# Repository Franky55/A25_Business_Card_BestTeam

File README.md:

# C3I A25\_Business\_Card

Concours de Conception de Circuits Imprimés – Université de Sherbrooke, Automne 2025

## Thème : Carte professionnelle (Business Card)

Bienvenue à la compétition de conception de PCB de l’Université de Sherbrooke, édition automne 2025 !
Cette année, le défi est de transformer la carte professionnelle traditionnelle en un **objet électronique unique, créatif et fonctionnel**.
Votre mission : concevoir un PCB au format carte de visite qui intègre des fonctionnalités innovantes, esthétiques et utiles dans un contexte professionnel réel.

---

## Déroulement

* **25 août** : Lancement de la compétition et ouverture des inscriptions
* **3 octobre** : Date limite d’inscription
* **10 octobre** : Date limite de sélection d’idée (formulaire fourni sur GitHub et Discord)
* **25 août au 31 décembre 23h59** : Période de conception et développement
* **Dates de commande des PCB et pièces** :

  * 19 septembre\* (LCSC)
  * 3 octobre\* (LCSC)
  * 17 octobre\* (LCSC)
  * 31 octobre\* (LCSC)
  * 14 novembre
  * 28 novembre
  * 12 décembre\*\* (commande finale, réception non garantie avant la fin)
* **Décembre** : Finalisation des projets
* **31 décembre 23h59** : Remise finale (schémas, Gerber, BOM, photos, doc)
* **5 janvier 2026** : Journée de l’événement et présentations publiques

---

### Répertoire "Template"  
Le répertoire "Template" contient tous les documents à remplir pour participer à la compétition. Vous y trouverez :  
- Formulaire d'idée (à remplir)
- Formulaire d'inscription (à remplir)
- Condition et termes de l'inscription
- TEMPLATE de PowerPoint
- TEMPLATE pour la documentation

---

### Répertoires code, elec et mech  
Chacun de ces répertoires contient de la documentation de départ pour vous guider. Consultez la section "doc". Ces répertoires sont également là pour vous aider à vous organiser lors du développement de votre règle.

---

### Comment forker le dépôt

1. Accédez au dépôt GitHub officiel à l'adresse suivante : `https://github.com/CCI-udes/H25_Pomodoro`.
2. Cliquez sur le bouton "Fork" en haut à droite de la page du dépôt.
3. Sélectionnez votre propre compte GitHub comme destination du fork.
4. Clonez le dépôt forké sur votre machine locale en utilisant la commande suivante :
   ```bash
   git clone https://github.com/<votre-utilisateur>/E25_Wearable.git
   ```

---

## Règlement

* Équipes de **1 à 3 personnes**
* Frais de participation : **10 \$ / membre** OU **courriel de commandite** (gabarits fournis)
* Dimensions maximales PCB : **88,9 mm x 50,8 mm**
* BOM maximum : **50 \$**
* Coût de développement total : **125 \$**
* Utilisation de **DevBoard permise** (pénalité de points si dans la version finale)
* Tous les types de composants acceptés (Bluetooth, NFC, OLED, etc.)
* Batterie rechargeable permise si formation suivie et protocole respecté
* Objectif : **s’amuser et apprendre** !

---

## Remise

Chaque équipe doit fournir via son fork GitHub :

* Schéma électrique (PDF)
* Fichiers Gerber du PCB + projet EDA OU PDF coloré des couches
* Photo(s) du PCB assemblé (avec et sans boîtier)
* BOM conforme aux normes C3I
* Documentation complète du projet

---

## Évaluation

Les projets seront notés sur un total de **250 points**, selon :

* **Idée \[15 pts]** (juges + vote des participants)
* **Fonctionnalité \[35 pts]** (implémentation et compréhension)
* **Complexité \[45 pts]** (hardware + software)
* **Gestion des ressources \[25 pts]** (BOM + commandes)
* **Démonstration \[55 pts]** (oral, écrit, esthétique)
* **Conception électronique \[75 pts]** (choix composants, schéma, PCB, assemblage, soudures)

---

## Prix

* 🏆 **Prix de conception** – Total 250 pts
* ⚡ **Prix du gningnégnieur** – Total 170 pts (créativité et apprentissage valorisés)
* 💼 **Prix du vendeur** – Total 125 pts (gestion, organisation, finition)

---

## Ressources utiles

* **Microcontrôleurs recommandés** : ESP32-C3, ESP32-S3, RP2040, RP2350, ch32v003
* **Logiciels de conception** : KiCad, Altium, EasyEDA (+ tutoriels fournis dans le doc)
* **Idées de business cards électroniques** : [Hackaday](https://hackaday.com/tag/pcb-business-card/), [Reddit](https://www.reddit.com/r/PCB/comments/14jk8cz/pcb_business_card_ideas/), [Exemples NFC](https://www.instructables.com/PCB-Business-Card-With-NFC/)
* **Discord** : [Lien d’invitation](https://discord.gg/xeSqf3N3Hw)

---

## Contacts

* Jacob Turcotte – Président – `Jacob.Turcotte@usherbrooke.ca`
* Miriam Caisse – Vice-présidente – `Miriam.Caisse@usherbrooke.ca`
* Jordan Gagnon – Trésorier – `Jordan.Gagnon@usherbrooke.ca`
* Céleste-Lyi Martel – Marketing – `Celeste-lyi.martel@usherbrooke.ca`

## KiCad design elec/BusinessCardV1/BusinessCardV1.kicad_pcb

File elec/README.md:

# Répertoire "elec" - CCI UdeS A24_ruler

Bienvenue dans le répertoire `elec` du projet **A24_ruler** pour la compétition de conception de PCB de l'Université de Sherbrooke, automne 2024.

## Objectif

Ce répertoire est destiné à contenir toute la documentation et les fichiers nécessaires à la conception électronique de la "règle" que vous allez créer pour cette compétition. Vous y trouverez des schémas, des fichiers de conception de PCB, et des ressources pour vous aider à concevoir et à réaliser vos circuits imprimés.

## Ressources

- [KiCad](https://www.kicad.org/) : Outil open-source pour la conception de PCB.
- [EasyEDA](https://easyeda.com/) : Outil de conception de PCB en ligne avec une interface conviviale.
- [Altium Designer](https://www.altium.com/altium-designer) : Solution professionnelle pour la conception de PCB avec des fonctionnalités avancées.

- [Digi-Key](https://www.digikey.com/) : Distributeur de composants électroniques.
- [Mouser Electronics](https://www.mouser.com/) : Distributeur de composants électroniques.
- [LCSC](https://www.lcsc.com/) : Distributeur de composants électroniques avec des prix compétitifs.

## Contributions

Lorsque vous apportez des modifications, assurez-vous de :
- Créer une branche spécifique pour vos changements.
- Soumettre une pull request une fois que vous êtes prêt pour une revue de code.

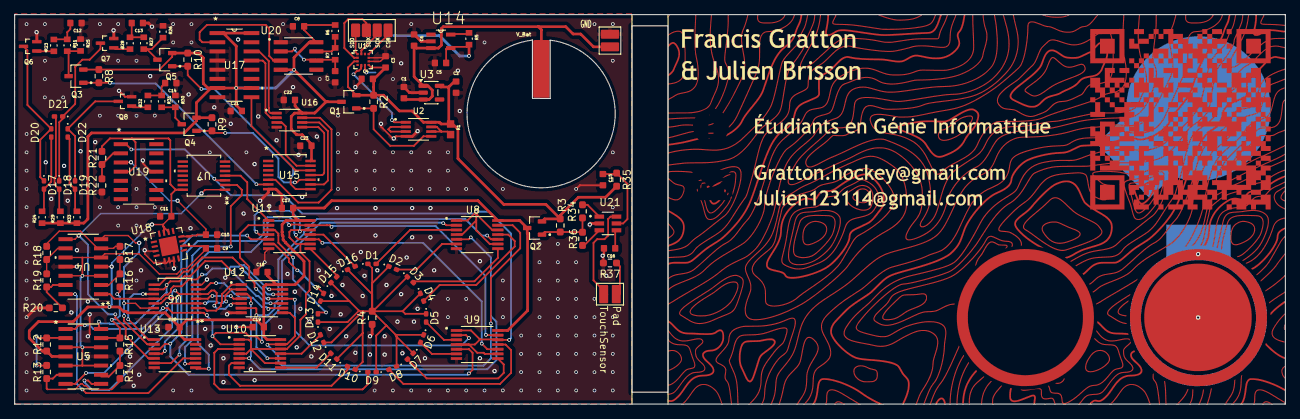
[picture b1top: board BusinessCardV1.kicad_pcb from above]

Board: 2 copper layers, 176.2 x 54.0 mm, 117 parts (1 on the bottom side), 102 nets.

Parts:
C1, C2, C3, C4, C8, C12, C13, C14, C17, C18, C19, C20, C21, C22, C23: 1uf; CAPC1608X90N
C5, C6: 4u7; CAPC1608X90N
C7: 1u; CAPC1608X90N
C9, C10, C11: CL10C471JB8NNNC; CAPC1608X90N
C15: 4.7uf; CAPC1608X90N
C16: 10uf; CAPC1608X90N
D1, D2, D3, D4, D5, D6, D7, D8, D9, D10, D11, D12, D13, D14, D15, D16, D17, D18, D19, D20, D21, D22: QBLP595-R; LED_0402_1005Metric_Pad0.77x0.64mm_HandSolder
J1: 61300411121; HEADER1x4_SMD
J2, J3, J4: 6130XX11121_61300211121; Header1x2_SMD
J5: 6130XX11121_61300211121; SMD_Header
Q1, Q2, Q3, Q4, Q5: DMG2305UX-7; SOT91P240X110-3N_DMG2305UX-7
Q6, Q7, Q8: DMG1012UW-7; SOT65P222X110-3N
R1: 100k; RESC1607X60N
R2, R3, R8, R9, R10: 1M; R_0603_1608Metric_Pad0.98x0.95mm_HandSolder
R4: 680; R_0603_1608Metric_Pad0.98x0.95mm_HandSolder
R5: 69K8; RESC1608X55N
R6: 20k; RESC1608X55N
R7: 700k; RESC1608X55N
R11, R27, R31: 250k; RESC1608X55N
R12, R13, R14, R15, R16, R17, R18, R19, R20, R21, R22, R34, R36, R37: 0; R_0603_1608Metric_Pad0.98x0.95mm_HandSolder
R23, R28, R32: 10; RESC1608X55N
R24, R29, R33: 180; RESC1608X55N
R25, R26, R30: 1.8M; RESC1608X55N
R35: 42.2; R_0603_1608Metric_Pad0.98x0.95mm_HandSolder
U1: *; XDCR_BMA400
U2: SN74LVC2G74DCTR; SOP65P400X130-8N
U3: TPS7A0233DBVR; SOT-23-5
U4, U5, U19: TLV8544DR; D14_TEX
U6, U7, U15: TC4069UBFTEL_N; TSSOP14_TOS
U8, U9, U10, U11, U12, U13: SN74LVC08APWR; SOP65P640X120-14N
U14: MCP73831T-2DCI_OT; SOT95P270X145-5N
U16: SN74LVC1G139DCTR; SOP65P400X130-8N
U17: SN74LV161ADR
U18: ADXL327BCPZ; CP_16_5A_ADI
U20: TLC555CDR; SOIC127P599X175-8N
U21: IQS228B00000000TSR; SOT95P280X100-6N
U22: TPD12S520DBT; design

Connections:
+3.3V: C2.2, C3.2, C4.2, Q1.2, Q2.2, R1.1, R2.1, R3.1, R35.2, U1.3 (VDDIO), U1.7 (VDD), U2.8 (VCC), U3.5 (OUT)
ADXL_X_OUT: C10.1, U18.12 (XOUT), U19.3 (+INA)
ADXL_Y_OUT: C9.1, U4.3 (+INA), U4.5 (+INB), U4.10 (+INC), U4.12 (+IND), U5.3 (+INA), U5.5 (+INB), U5.10 (+INC), U5.12 (+IND), U18.10 (YOUT)
Blue_LED: U15.5, U16.7 (Y0)
CLK_Sequence: U17.2 (CLK), U20.3 (OUT)
Charge_Blue_Cap: Q3.3, R11.2, R25.2
Charge_Green_Cap: Q5.3, R26.2, R27.2
Charge_Red_Cap: Q4.3, R30.2, R31.2
DISCH: R6.1, R7.2, U20.7 (DISCH)
GND: C1.1, C2.1, C3.1, C4.1, C5.1, C6.1, C7.1, C8.1, C9.2, C10.2, C11.1, C12.1, C13.1, C14.1, C15.2, C16.2, C17.1, C18.1, C19.1, C20.1, C21.1, C22.1, C23.1, J2.1, J3.1, Q6.2, Q7.2, Q8.2, R4.1, R20.2, R22.2, R25.1, R26.1, R30.1, R37.1, U1.8 (GNDIO), U1.9 (GND), U2.4 (GND), U3.2 (GND), U4.11 (V), U5.11 (V), U6.7, U7.7, U8.7 (GND), U9.7 (GND), U10.7 (GND), U11.7 (GND), U12.7 (GND), U13.7 (GND), U14.2 (VSS), U15.7, U16.4 (GND), U17.3 (A), U17.4 (B), U17.5 (C), U17.6 (D), U17.8 (GND), U18.3 (COM), U18.5 (COM), U18.6 (COM), U18.7 (COM), U19.11 (V), U20.1 (GND), U21.2 (GND)
Green_LED: U15.9, U16.6 (Y1)
INT_CLK: U1.5 (INT1), U2.1 (CLK)
LSB_Counter: U16.1 (A), U17.14 (QA)
MSB_Counter: U16.2 (B), U17.13 (QB)
unnamed: C12.2, R11.1, R23.2
unnamed: C13.2, R27.1, R28.2
unnamed: C14.2, R31.1, R32.2
unnamed: D1.2 (ANODE_(+)), U8.3 (1Y)
unnamed: D1.1 (CATHODE_(-)), D2.1 (CATHODE_(-)), D3.1 (CATHODE_(-)), D4.1 (CATHODE_(-)), D5.1 (CATHODE_(-)), D6.1 (CATHODE_(-)), D7.1 (CATHODE_(-)), D8.1 (CATHODE_(-)), D9.1 (CATHODE_(-)), D10.1 (CATHODE_(-)), D11.1 (CATHODE_(-)), D12.1 (CATHODE_(-)), D13.1 (CATHODE_(-)), D14.1 (CATHODE_(-)), D15.1 (CATHODE_(-)), D16.1 (CATHODE_(-)), R4.2
unnamed: D2.2 (ANODE_(+)), U8.6 (2Y)
unnamed: D3.2 (ANODE_(+)), U8.8 (3Y)
unnamed: D4.2 (ANODE_(+)), U8.11 (4Y)
unnamed: D5.2 (ANODE_(+)), U9.3 (1Y)
unnamed: D6.2 (ANODE_(+)), U9.6 (2Y)
unnamed: D7.2 (ANODE_(+)), U9.8 (3Y)
unnamed: D8.2 (ANODE_(+)), U9.11 (4Y)
unnamed: D9.2 (ANODE_(+)), U10.3 (1Y)
unnamed: D10.2 (ANODE_(+)), U10.6 (2Y)
unnamed: D11.2 (ANODE_(+)), U10.8 (3Y)
unnamed: D12.2 (ANODE_(+)), U10.11 (4Y)
unnamed: D13.2 (ANODE_(+)), U11.3 (1Y)
unnamed: D14.2 (ANODE_(+)), U11.6 (2Y)
unnamed: D15.2 (ANODE_(+)), U11.8 (3Y)
unnamed: D16.2 (ANODE_(+)), U11.11 (4Y)
unnamed: D17.2 (ANODE_(+)), D20.2 (ANODE_(+)), R24.2
unnamed: D17.1 (CATHODE_(-)), D20.1 (CATHODE_(-)), Q6.3
unnamed: D18.2 (ANODE_(+)), D21.2 (ANODE_(+)), R29.2
unnamed: D18.1 (CATHODE_(-)), D21.1 (CATHODE_(-)), Q7.3
unnamed: D19.2 (ANODE_(+)), D22.2 (ANODE_(+)), R33.2
unnamed: D19.1 (CATHODE_(-)), D22.1 (CATHODE_(-)), Q8.3
unnamed: Q6.1, R23.1
unnamed: Q7.1, R28.1
unnamed: Q8.1, R32.1
unnamed: R1.2, U2.6 (~CLR), U2.7 (~PRE)
unnamed: R16.2, R17.1, U4.2 (INA)
unnamed: R17.2, R18.1, U4.6 (INB)
unnamed: R18.2, R19.1, U4.9 (INC)
unnamed: R19.2, R20.1, U4.13 (IND)
unnamed: R12.2, R13.1, U5.2 (INA)
unnamed: R13.2, R14.1, U5.6 (INB)
unnamed: R14.2, R15.1, U5.9 (INC)
unnamed: R15.2, R16.1, U5.13 (IND)
unnamed: R5.1, U14.5 (PROG)
unnamed: R21.2, R22.1, U19.2 (INA)
unnamed: R36.2, U21.3 (CTRL/ND)
unnamed: R34.2, U21.1 (OUT)
unnamed: C15.1, R35.1, U21.5 (VDDHI)
unnamed: C16.1, U21.4 (VREG)
Pad: J4.2, R37.2
Power3V3: C8.2, C21.2, C22.2, C23.2, Q1.3, Q3.2, Q4.2, Q5.2, R6.2, R8.1, R9.1, R10.1, R24.1, R29.1, R33.1, U15.14, U16.8 (VCC), U17.1 (*CLR), U17.7 (ENP), U17.10 (ENT), U17.16 (VCC), U20.4 (RESET), U20.8 (VDD)
Q: Q1.1, R2.2, U2.5 (Q)
Red_LED: U15.11, U16.5 (Y2)
Reset: U15.13, U16.3 (Y3)
RingBTN: Q2.1, R3.2, R34.1, R36.1
RingPower: C11.2, C17.2, C18.2, C19.2, C20.2, Q2.3, R12.1, R21.1, U4.4 (V+), U5.4 (V+), U6.14, U7.14, U8.14 (VCC), U9.14 (VCC), U10.14 (VCC), U11.14 (VCC), U12.14 (VCC), U13.14 (VCC), U18.14 (VS), U18.15 (VS), U19.4 (V+)
SCX: J1.03, U1.12 (SCX)
SDO: J1.01, U1.1 (SDO)
SDX: J1.02, U1.2 (SDX)
SolarPower: C5.2, J2.2, R5.2, U14.4 (VDD)
TRIG: C7.2, R7.1, U20.2 (TRIG), U20.6 (THRES)
TouchSensor: J4.1, U21.6 (CX)
V_Bat: C1.2, C6.2, J3.2, J5.1, U3.1 (IN), U3.3 (EN), U14.3 (VBAT)
Y1: U5.1 (OUTA), U6.1, U8.2 (1B), U10.2 (1B)
Y2: U8.5 (2B), U10.5 (2B), U12.3 (1Y)
Y3: U8.10 (3B), U10.10 (3B), U12.6 (2Y)
Y4: U8.13 (4B), U10.13 (4B), U12.8 (3Y)
Y5: U9.2 (1B), U11.2 (1B), U12.11 (4Y)
Y6: U9.5 (2B), U11.5 (2B), U13.3 (1Y)
Y7: U9.10 (3B), U11.10 (3B), U13.6 (2Y)
Y8: U9.13 (4B), U11.13 (4B), U13.8 (3Y)
op_y2: U5.7 (OUTB), U6.3, U12.2 (1B)
op_y3: U5.8 (OUTC), U6.5, U12.5 (2B)
op_y4: U5.14 (OUTD), U6.9, U12.10 (3B)
op_y5: U4.1 (OUTA), U6.11, U12.13 (4B)
op_y6: U4.7 (OUTB), U6.13, U13.2 (1B)
op_y7: U4.8 (OUTC), U7.1, U13.5 (2B)
op_y8: U4.14 (OUTD), U13.10 (3B)
x: U7.3, U8.1 (1A), U8.4 (2A), U8.9 (3A), U8.12 (4A), U9.1 (1A), U9.4 (2A), U9.9 (3A), U9.12 (4A), U19.1 (OUTA)
~Blue_LED: Q3.1, R8.2, U15.6
~CSB: J1.04, U1.10 (~CSB)
~Green_LED: Q5.1, R10.2, U15.8
~Q: U2.2 (D), U2.3 (~Q)
~Red_LED: Q4.1, R9.2, U15.10
~Reset: U15.12, U17.9 (*LOAD)
~x: U7.4, U10.1 (1A), U10.4 (2A), U10.9 (3A), U10.12 (4A), U11.1 (1A), U11.4 (2A), U11.9 (3A), U11.12 (4A)
~y1: U6.2, U12.1 (1A)
~y2: U6.4, U12.4 (2A)
~y3: U6.6, U12.9 (3A)
~y4: U6.8, U12.12 (4A)
~y5: U6.10, U13.1 (1A)
~y6: U6.12, U13.4 (2A)
~y7: U7.2, U13.9 (3A)

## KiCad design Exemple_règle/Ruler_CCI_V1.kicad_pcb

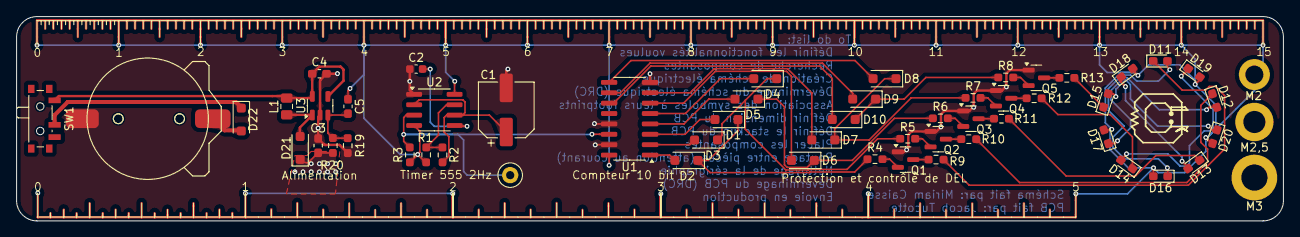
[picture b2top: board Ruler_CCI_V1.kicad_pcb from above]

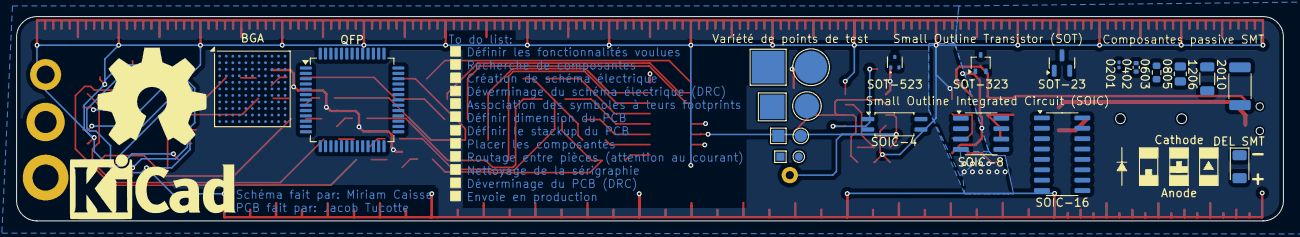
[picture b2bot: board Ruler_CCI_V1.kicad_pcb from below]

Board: 2 copper layers, 155.0 x 25.0 mm, 71 parts (15 on the bottom side), 46 nets.

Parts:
0201: R_0201_0603Metric
0402: R_0402_1005Metric
0603: R_0603_1608Metric
0805: R_0805_2012Metric
1206: R_1206_3216Metric
2010: R_2010_5025Metric
BGA: BGA-121_9.0x9.0mm_Layout11x11_P0.8mm_Ball0.4mm_Pa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; BGA-121_9.0x9.0mm_Layout11x11_P0.8mm_Ball0.4mm_Pad0.35mm_NS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
BT1: Battery; BAT_SMD_CR1220
C1: 150u; CP_Elec_6.3x7.7
C2: 10n; C_0603_1608Metric
C3: 1u; L_0603_1608Metric_Pad1.05x0.95mm_HandSolder
C4: 4.7u; L_0603_1608Metric_Pad1.05x0.95mm_HandSolder
C5: 22p; L_0603_1608Metric_Pad1.05x0.95mm_HandSolder
D1, D2, D3, D4, D5, D6, D7, D8, D9, D10, D21, D22: 1N4007; D_SOD-123F
D11, D12, D13, D14, D15: LED_GREEN; D_0603_1608Metric_Pad1.05x0.95mm_HandSolder
D16, D17, D18, D19, D20: LED_YELLOW; D_0603_1608Metric_Pad1.05x0.95mm_HandSolder
DEL SMT: LED_1206_3216Metric
L1: 10u; L_0805_2012Metric_Pad1.15x1.40mm_HandSolder
M2: MountingHole_2.2mm_M2_DIN965_Pad
M2,5: MountingHole_2.7mm_M2.5_DIN965_Pad
M3: MountingHole_3.2mm_M3_DIN965_Pad
Q1, Q2, Q3, Q4, Q5: BC107; SOT-23
QFP: LQFP-52_10x10mm_P0.65mm
R1, R2: 1.6k; R_0603_1608Metric_Pad0.98x0.95mm_HandSolder
R3: 1k; R_0603_1608Metric_Pad0.98x0.95mm_HandSolder
R4, R5, R6, R7, R8: 470; R_0603_1608Metric_Pad0.98x0.95mm_HandSolder
R9, R10, R11, R12, R13: 169; R_0603_1608Metric_Pad0.98x0.95mm_HandSolder
R19: 500k; R_0603_1608Metric_Pad0.98x0.95mm_HandSolder
R20: 1.54M; R_0603_1608Metric_Pad0.98x0.95mm_HandSolder
SOIC-4: SOIC-4_4.55x2.6mm_P1.27mm
SOIC-8: SOIC-8_3.9x4.9mm_P1.27mm
SOIC-16: SOIC-16_3.9x9.9mm_P1.27mm
SOT-23: SOT-23
SOT-323: SOT-323_SC-70
SOT-523: SOT-523
SW1: SW_SPDT; SW_SPDT_PCM12
U1: 4017; SOP-16_3.9x9.9mm_P1.27mm
U2: NE555D; SOIC-8_3.9x4.9mm_P1.27mm
U3: TPS61041DBV; SOT-23-5

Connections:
+6.8V: C3.1, C5.1, D16.2 (A), D17.2 (A), D18.2 (A), D19.2 (A), D20.2 (A), D21.1 (K), R1.1, R3.1, R20.2, U1.16 (VDD), U2.4 (R), U2.8 (VCC)
GND: BT1.2 (-), C1.2, C2.2, C3.2, C4.2, Q1.1 (E), Q2.1 (E), Q3.1 (E), Q4.1 (E), Q5.1 (E), R19.1, U1.8 (VSS), U1.13 (CKEN), U1.15 (Reset), U2.1 (GND), U3.2 (GND)
LIGHT1: Q1.3 (C), R9.1
LIGHT2: Q2.3 (C), R10.1
LIGHT3: Q3.3 (C), R11.1
LIGHT4: Q4.3 (C), R12.1
LIGHT5: Q5.3 (C), R13.1
unnamed: BT1.1 (+), D22.2 (A)
unnamed: D1.1 (K), D2.1 (K), R4.1
unnamed: D3.1 (K), D4.1 (K), R5.1
unnamed: D5.1 (K), D6.1 (K), R6.1
unnamed: D7.1 (K), D8.1 (K), R7.1
unnamed: D9.1 (K), D10.1 (K), R8.1
unnamed: D11.2 (A), D16.1 (K)
unnamed: D11.1 (K), R9.2
unnamed: D12.2 (A), D17.1 (K)
unnamed: D12.1 (K), R10.2
unnamed: D13.2 (A), D18.1 (K)
unnamed: D13.1 (K), R11.2
unnamed: D14.2 (A), D19.1 (K)
unnamed: D14.1 (K), R12.2
unnamed: D15.2 (A), D20.1 (K)
unnamed: D15.1 (K), R13.2
unnamed: D21.2 (A), L1.2, U3.1 (SW)
unnamed: D22.1 (K), SW1.2 (B)
unnamed: Q1.2 (B), R4.2
unnamed: Q2.2 (B), R5.2
unnamed: Q3.2 (B), R6.2
unnamed: Q4.2 (B), R7.2
unnamed: Q5.2 (B), R8.2
unnamed: C4.1, L1.1, SW1.1 (A), U3.4 (EN), U3.5 (VIN)
unnamed: C2.1, U2.5 (CV)
unnamed: R1.2, R2.1, U2.7 (DIS)
unnamed: C1.1, R2.2, U2.2 (TR), U2.6 (THR)
unnamed: C5.2, R19.2, R20.1, U3.3 (FB)
OUT0: D1.2 (A), U1.3 (Q0)
OUT1: D3.2 (A), U1.2 (Q1)
OUT2: D5.2 (A), U1.4 (Q2)
OUT3: D7.2 (A), U1.7 (Q3)
OUT4: D9.2 (A), U1.10 (Q4)
OUT5: D2.2 (A), U1.1 (Q5)
OUT6: D4.2 (A), U1.5 (Q6)
OUT7: D6.2 (A), U1.6 (Q7)
OUT8: D8.2 (A), U1.9 (Q8)
OUT9: D10.2 (A), U1.11 (Q9)
PWM: R3.2, U1.14 (CLK), U2.3 (Q)

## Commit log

2025-08-25 redo push
2025-09-03 Fix and pdf push
2025-10-15 Ajout atelier
2025-10-18 Kicad created
2025-10-18 Added BMA400
2025-10-18 Big Ballz
2025-10-18 stage
2025-10-27 Started the power management
2025-10-27 forgot to close kicad before pushing
2025-10-27 Added header BMA400
2025-10-28 heheheha
2025-10-28 Power finished
2025-10-29 Timer and starting LED circuit of RGB
2025-10-29 Circle wiring
2025-10-31 Added a few things
2025-11-23 Added timer 555
2025-11-24 Je sais pas trop
2025-11-25 Finished LED fade
2025-11-26 Button working i guess i hope
2025-11-27 All footprint and start of PCB
2025-11-27 pcb fix + round led layup
2025-11-27 Started layout
2025-11-28 PCB art
2025-11-28 Missing update
2025-11-28 Pushé les poin zip
2025-11-28 Position made, but kicad lagging everytime i add a wire
2025-11-28 Push before destroying everything
2025-11-28 Easy part done, Glabel kind of worked
2025-11-28 PCB routed
2025-11-28 Gerber almost ready
2025-11-28 Everything is good
2026-01-03 Website Franky + Bobelbo
2026-01-03 website done
2026-01-04 Added config for the BMA400
2026-01-04 Remise WIP
2026-01-04 Update remise
2026-01-04 Gerbers
2026-01-04 Documentation
